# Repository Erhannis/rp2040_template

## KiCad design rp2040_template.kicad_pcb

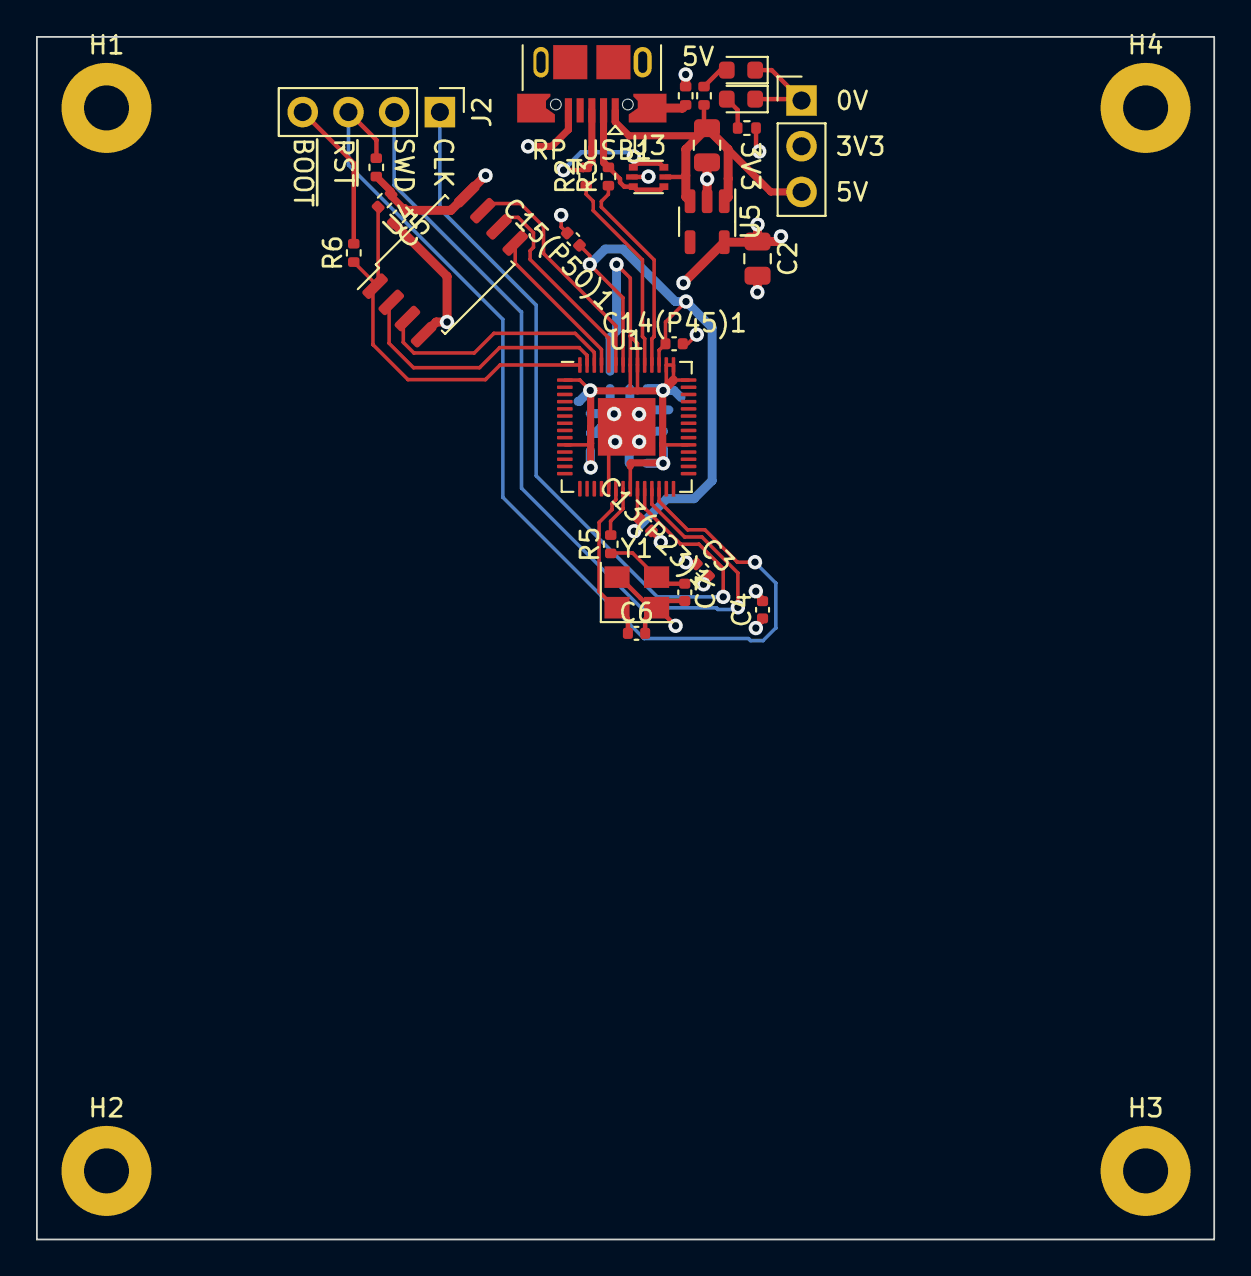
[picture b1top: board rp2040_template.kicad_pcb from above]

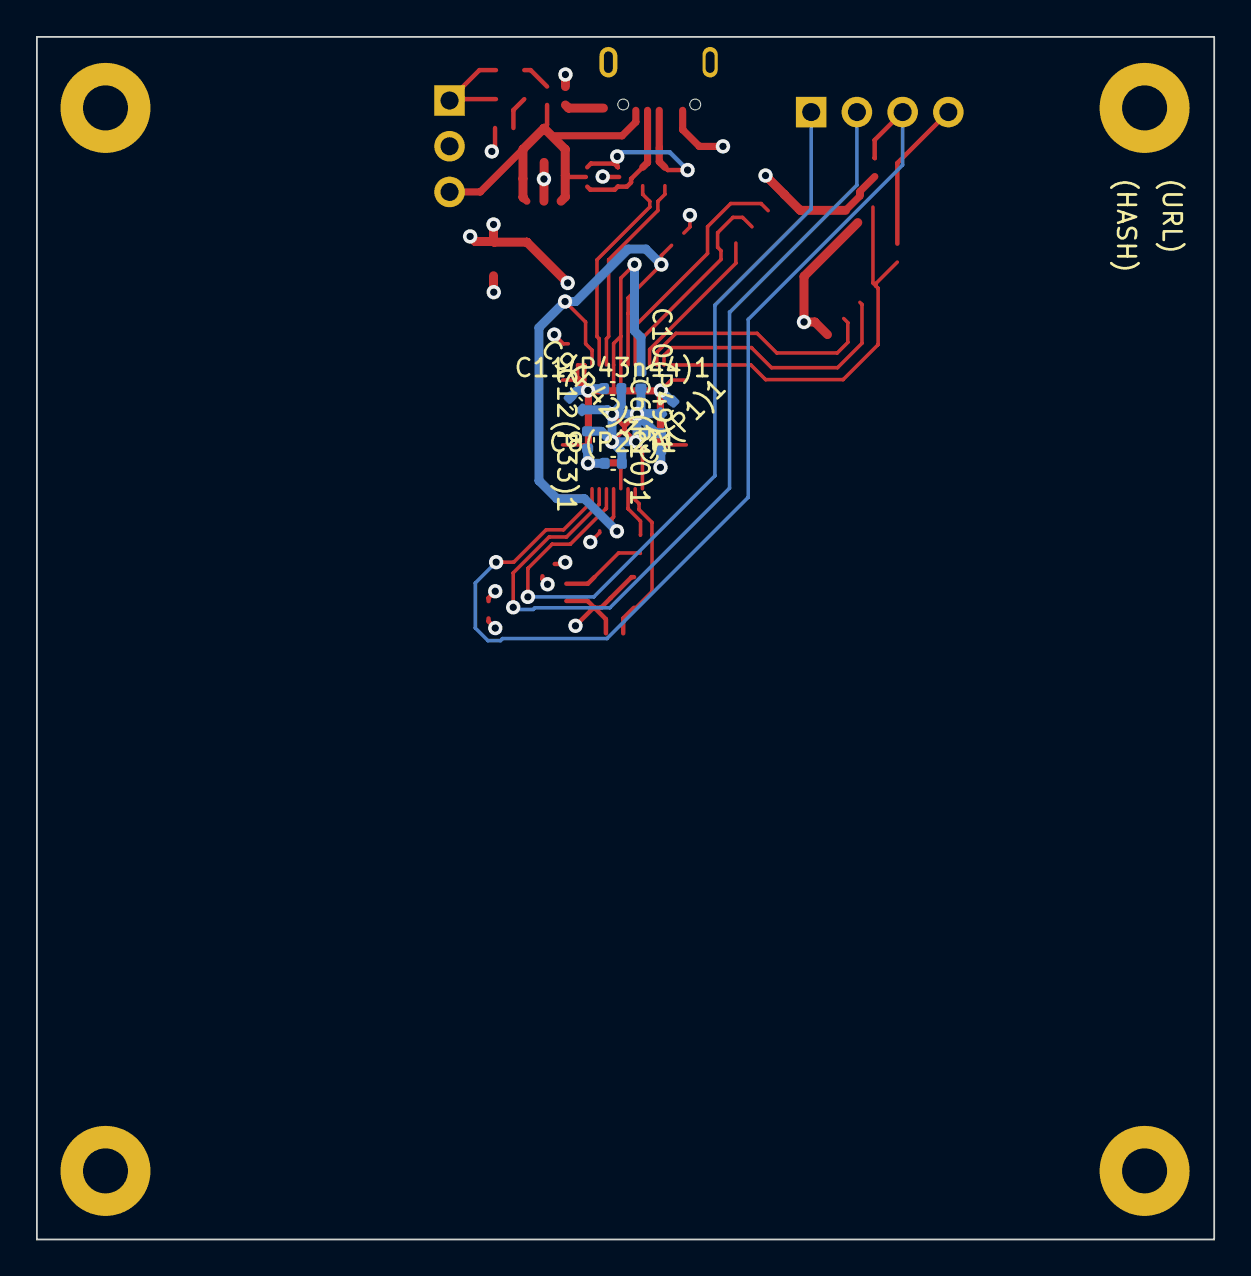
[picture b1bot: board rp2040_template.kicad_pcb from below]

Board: 4 copper layers, 65.4 x 66.8 mm, 40 parts (7 on the bottom side), 24 nets.

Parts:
C1, C2: 10uF; C_0805_2012Metric
C3, C4, C5, C6(P10)1, C7(P1)1, C8(P22)1, C9(P42)1, C10(P49)1, C12(P33)1, C13(P23)1, C15(P50)1: 100nF; C_0402_1005Metric
C6, C7: 35pF; C_0402_1005Metric
C11(P43n44)1, C14(P45)1: 1uF; C_0402_1005Metric
D1_UM1: LED(R); LED_0603_1608Metric
D2_UM1: LED(G); LED_0603_1608Metric
H1, H2, H3, H4: MountingHole_Pad; MountingHole_2.5mm_Pad
J1: Conn_01x03_Pin; PinHeader_1x03_P2.54mm_Vertical
J2: Conn_01x04_Pin; PinHeader_1x04_P2.54mm_Vertical
R1: 1M; R_0402_1005Metric
R2, R3: 27; R_0402_1005Metric
R4, R7: 10K; R_0402_1005Metric
R4_UM1, R5_UM1: 330; R_0402_1005Metric
R5: 1K; R_0402_1005Metric
R6: 1k; R_0402_1005Metric
RP_USB1: USB_B_Micro; USB_Micro-B_XKB_U254-051T-4BH83-F1S
U1: RP2040; QFN-56-1EP_7x7mm_P0.4mm_EP3.2x3.2mm
U3: USBLC6-2P6; SOT-666
U4: W25Q128JVS; SOIC-8_5.23x5.23mm_P1.27mm
U5: AP2112K-3.3; SOT-23-5
Y1: 12MHz; Crystal_SMD_3225-4Pin_3.2x2.5mm

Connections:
+1V2: C13(P23)1.1, C14(P45)1.1, C15(P50)1.1, U1.23 (DVDD), U1.45 (VREG_VOUT), U1.50 (DVDD)
+3V3: C2.1, C3.1, C4.1, C5.1, C6(P10)1.1, C7(P1)1.1, C8(P22)1.1, C9(P42)1.1, C10(P49)1.1, C11(P43n44)1.1, C12(P33)1.1, J1.2, R4.1, R5_UM1.1, R7.2, U1.1 (IOVDD), U1.10 (IOVDD), U1.22 (IOVDD), U1.33 (IOVDD), U1.42 (IOVDD), U1.43 (ADC_AVDD), U1.44 (VREG_IN), U1.48 (USB_VDD), U1.49 (IOVDD), U4.8 (VCC), U5.5 (VOUT)
+5V: C1.1, J1.3, R4_UM1.1, RP_USB1.1 (VBUS), U3.5 (VBUS), U5.1 (VIN), U5.3 (EN)
/QSPI_CS: R6.1, R7.1, U1.56 (QSPI_SS), U4.1 (~CS)
/QSPI_DATA[0]: U1.53 (QSPI_SD0), U4.5 (DI(IO0))
/QSPI_DATA[1]: U1.55 (QSPI_SD1), U4.2 (DO(IO1))
/QSPI_DATA[2]: U1.54 (QSPI_SD2), U4.3 (IO2)
/QSPI_DATA[3]: U1.51 (QSPI_SD3), U4.7 (IO3)
/QSPI_SCK: U1.52 (QSPI_SCLK), U4.6 (CLK)
/RP_SWCLK: J2.1, U1.24 (SWCLK)
/RP_SWD: J2.2, U1.25 (SWD)
/RP_UD+: R2.1, U1.47 (USB_DP)
/RP_UD-: R3.1, U1.46 (USB_DM)
/USB_BOOT: J2.4, R6.2
/~RESET: J2.3, R4.2, U1.26 (RUN)
GND: C1.2, C2.2, C3.2, C4.2, C5.2, C6.2, C6(P10)1.2, C7.2, C7(P1)1.2, C8(P22)1.2, C9(P42)1.2, C10(P49)1.2, C11(P43n44)1.2, C12(P33)1.2, C13(P23)1.2, C14(P45)1.2, C15(P50)1.2, D1_UM1.1 (K), D2_UM1.1 (K), H1.1, H2.1, H3.1, H4.1, J1.1, R1.1, RP_USB1.5 (GND), U1.19 (TESTEN), U1.57 (GND), U3.2 (GND), U4.4 (GND), U5.2 (GND), Y1.2, Y1.4
unnamed: C7.1, R5.1, Y1.3
unnamed: D1_UM1.2 (A), R4_UM1.2
unnamed: D2_UM1.2 (A), R5_UM1.2
unnamed: R2.2, RP_USB1.3 (D+), U3.1 (I/O1), U3.6 (I/O1)
unnamed: R3.2, RP_USB1.2 (D-), U3.3 (I/O2), U3.4 (I/O2)
unnamed: R1.2, RP_USB1.6 (Shield)
unnamed: C6.1, U1.20 (XIN), Y1.1
unnamed: R5.2, U1.21 (XOUT)

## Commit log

2023-10-17 KiCAD template for RP2040 with micro usb connector.
2024-05-14 updated KiCAD to 8.0
2024-05-14 Swapped crystal caps for ones more in stock
2024-05-14 Removed titles
2024-07-11 Added power LEDs
2024-07-11 One of the LEDs was out of stock; replaced with a more plentiful one.
